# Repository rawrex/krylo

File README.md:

**Krylo** (*"wing"* in Russian) is a 32 key column-staggered split keyboard running [ZMK](https://zmk.dev/)

Core ideas that motivated the project:
- (My) pinky moves to the side better than it reaches forward to the upper row.
- (My) index finger is also able to move to the side, but it is not comfortable to move to the side and down.
- Single PCB symmetrical definition for both sides of the split.

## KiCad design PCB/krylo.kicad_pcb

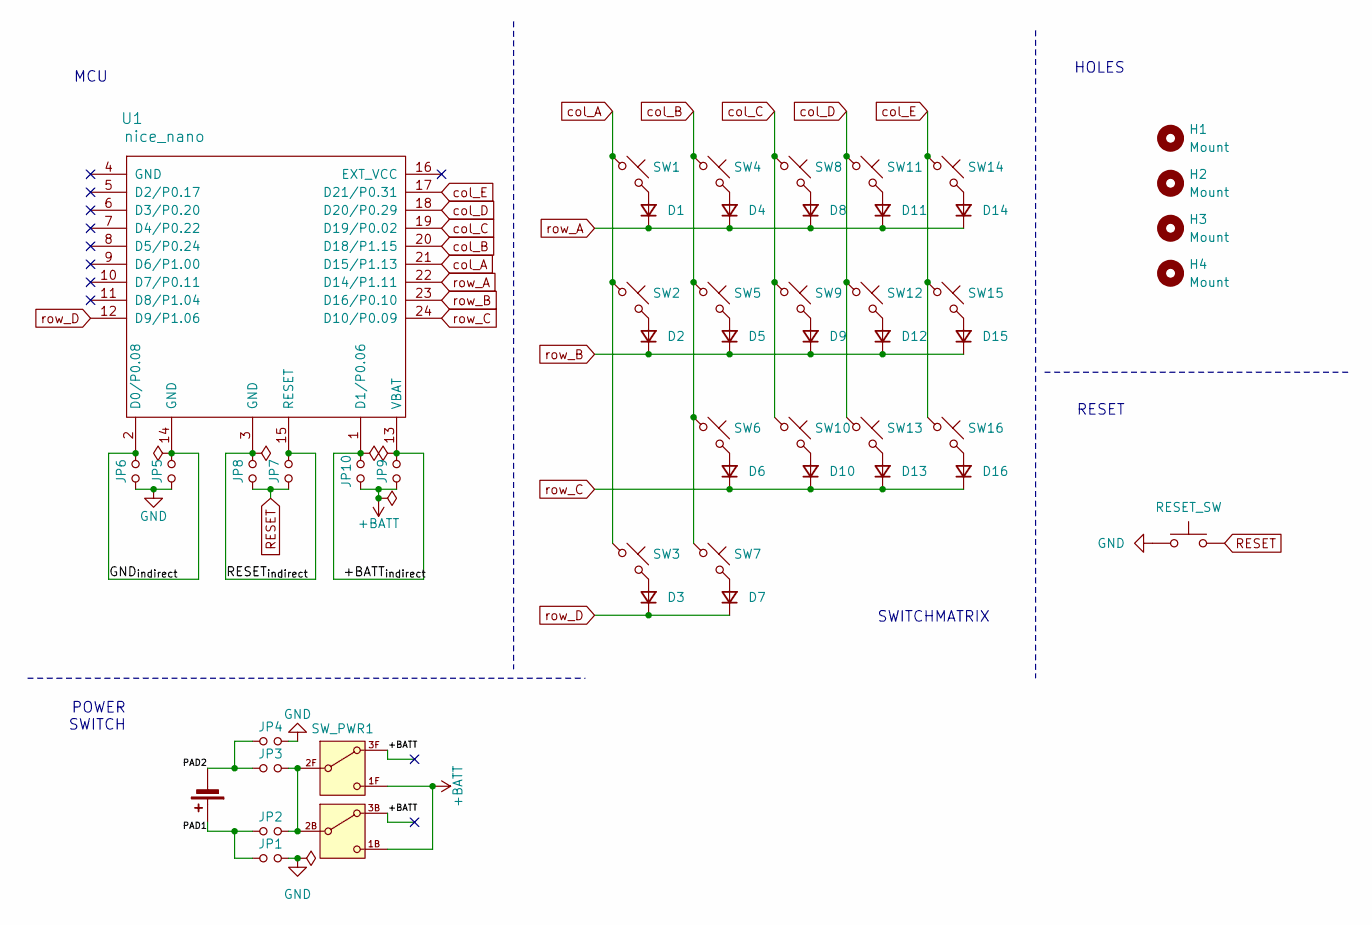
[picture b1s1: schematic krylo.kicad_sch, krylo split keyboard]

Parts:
BT1: MOLEX_C
D1, D2, D3, D4, D5, D6, D7, D8, D9, D10, D11, D12, D13, D14, D15, D16: D_SOD123
H1, H2, H3, H4: Mount
JP1, JP2, JP3, JP4, JP5, JP6, JP7, JP8, JP9, JP10: Jumper
RESET1: RESET_SW; ResetSW
SW1, SW2, SW3, SW4, SW5, SW6, SW7, SW8, SW9, SW10, SW11, SW12, SW13, SW14, SW15, SW16: Switch
SW_PWR1: MSK12C02
U1: nice_nano

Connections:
+BATT: JP9.1, JP10.1, SW_PWR1.1B (C_back), SW_PWR1.1F (C_front), SW_PWR1.3B (A_back), SW_PWR1.3F (A_front)
/+BATT_{indirect}: JP9.2, JP10.2, U1.1 (D1/P0.06), U1.13 (VBAT)
/GND_{indirect}: JP5.2, JP6.2, U1.2 (D0/P0.08), U1.14 (GND)
/PAD1: BT1.1 (+), JP1.1, JP2.1
/PAD2: BT1.2 (-), JP3.1, JP4.1
/RESET_{indirect}: JP7.2, JP8.2, U1.3 (GND), U1.15 (RESET)
GND: JP1.2, JP4.2, JP5.1, JP6.1, RESET1.1
unnamed: D1.2 (A), SW1.2
unnamed: D2.2 (A), SW2.2
unnamed: D3.2 (A), SW3.2
unnamed: D4.2 (A), SW4.2
unnamed: D5.2 (A), SW5.2
unnamed: D6.2 (A), SW6.2
unnamed: D7.2 (A), SW7.2
unnamed: D8.2 (A), SW8.2
unnamed: D9.2 (A), SW9.2
unnamed: D10.2 (A), SW10.2
unnamed: D11.2 (A), SW11.2
unnamed: D12.2 (A), SW12.2
unnamed: D13.2 (A), SW13.2
unnamed: D14.2 (A), SW14.2
unnamed: D15.2 (A), SW15.2
unnamed: D16.2 (A), SW16.2
unnamed: JP2.2, JP3.2, SW_PWR1.2B (B_back), SW_PWR1.2F (B_front)
RESET: JP7.1, JP8.1, RESET1.2
col_A: SW1.1, SW2.1, SW3.1, U1.21 (D15/P1.13)
col_B: SW4.1, SW5.1, SW6.1, SW7.1, U1.20 (D18/P1.15)
col_C: SW8.1, SW9.1, SW10.1, U1.19 (D19/P0.02)
col_D: SW11.1, SW12.1, SW13.1, U1.18 (D20/P0.29)
col_E: SW14.1, SW15.1, SW16.1, U1.17 (D21/P0.31)
row_A: D1.1 (K), D4.1 (K), D8.1 (K), D11.1 (K), D14.1 (K), U1.22 (D14/P1.11)
row_B: D2.1 (K), D5.1 (K), D9.1 (K), D12.1 (K), D15.1 (K), U1.23 (D16/P0.10)
row_C: D6.1 (K), D10.1 (K), D13.1 (K), D16.1 (K), U1.24 (D10/P0.09)
row_D: D3.1 (K), D7.1 (K), U1.12 (D9/P1.06)

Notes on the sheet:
SWITCHMATRIX
POWER SWITCH
HOLES
MCU
RESET

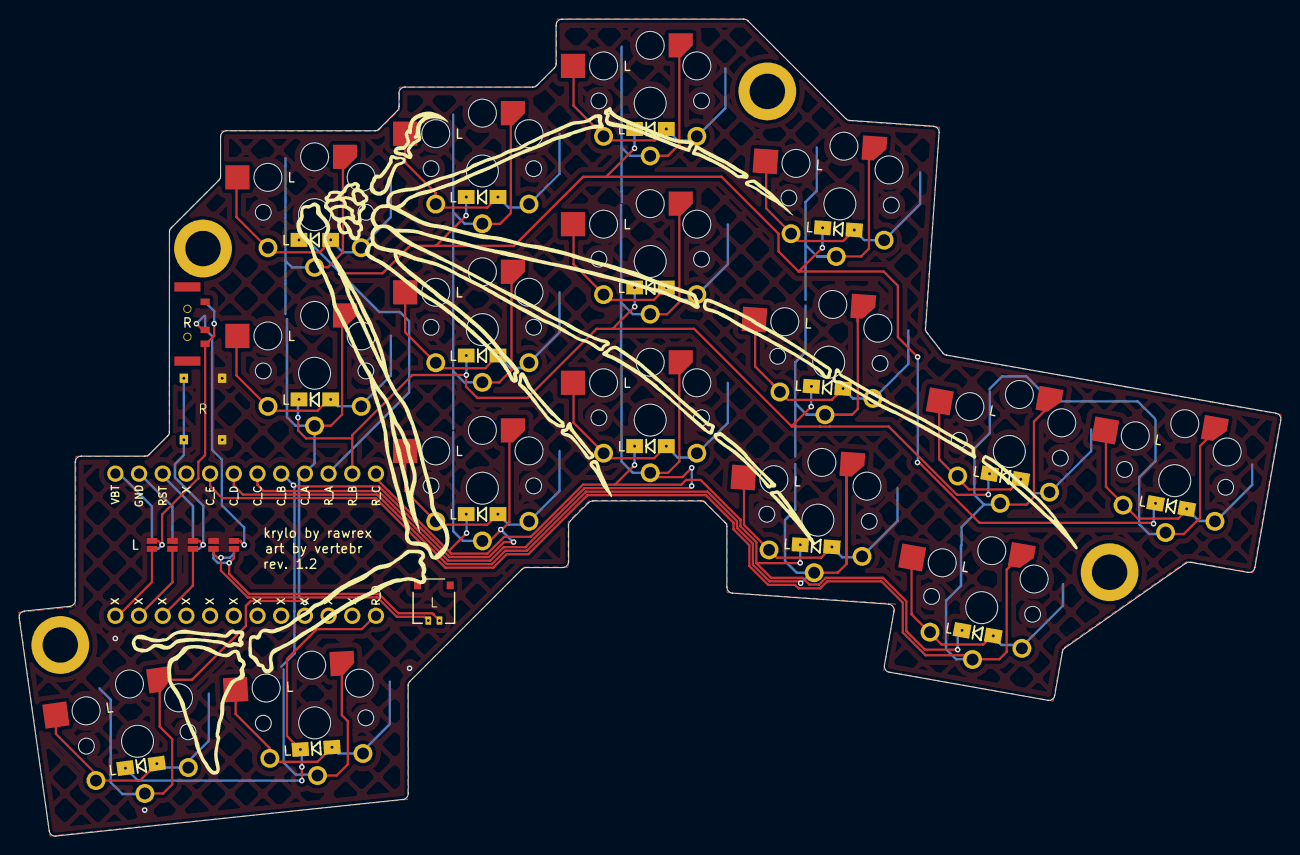
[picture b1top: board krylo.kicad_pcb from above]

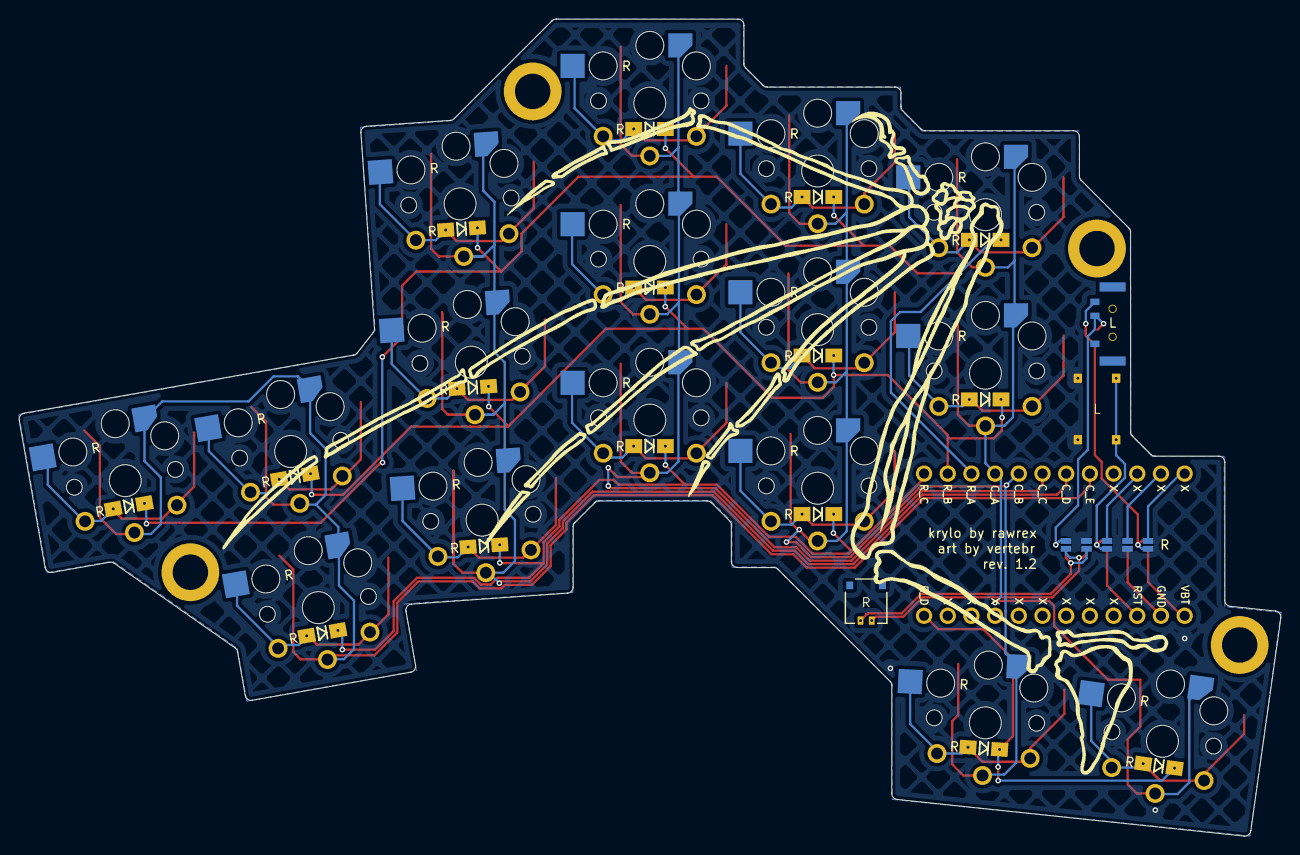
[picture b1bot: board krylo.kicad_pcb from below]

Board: 2 copper layers, 135.3 x 87.6 mm, 51 parts (5 on the bottom side), 34 nets.

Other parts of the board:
INFO: Info

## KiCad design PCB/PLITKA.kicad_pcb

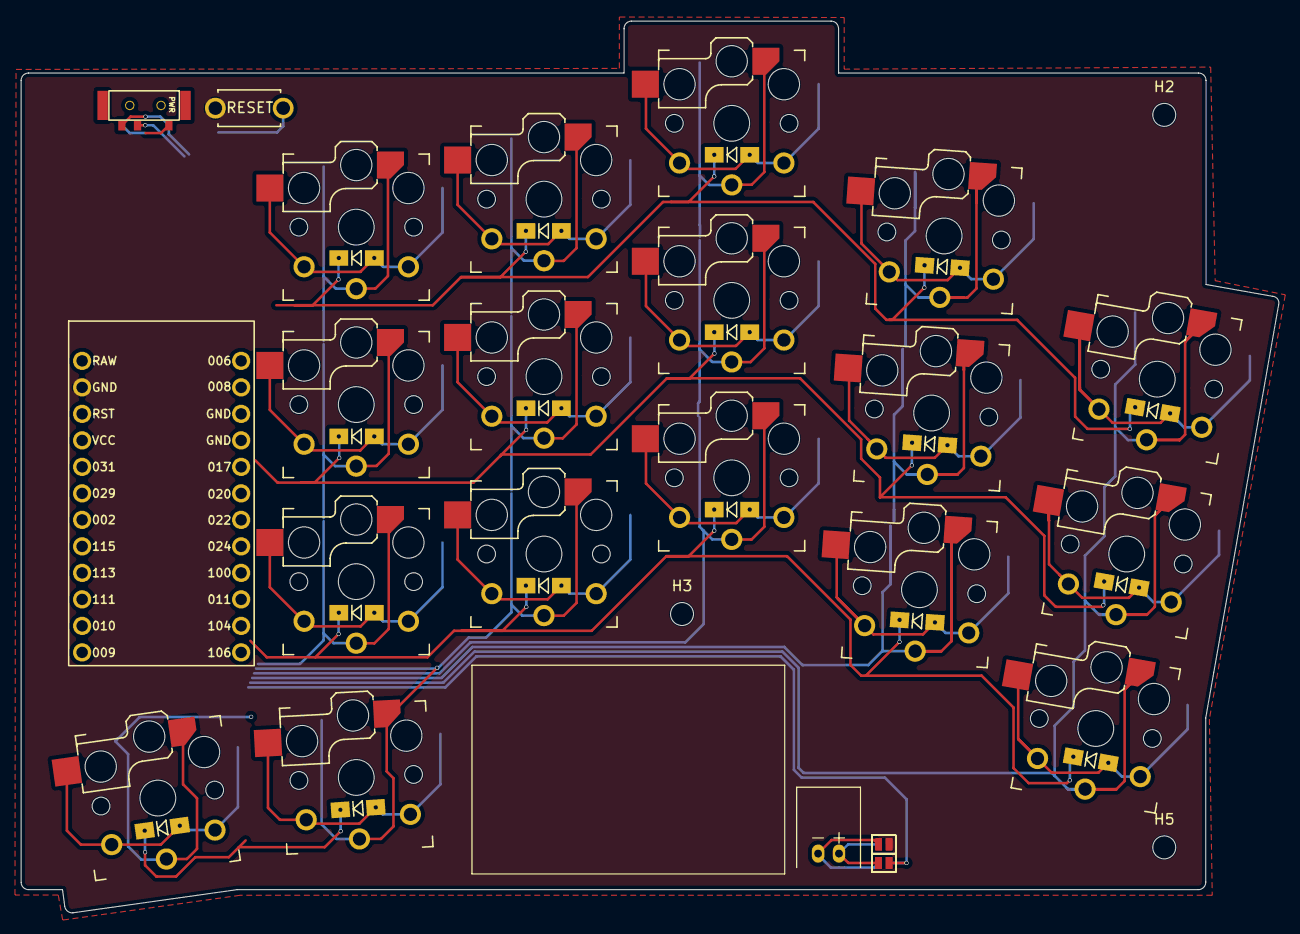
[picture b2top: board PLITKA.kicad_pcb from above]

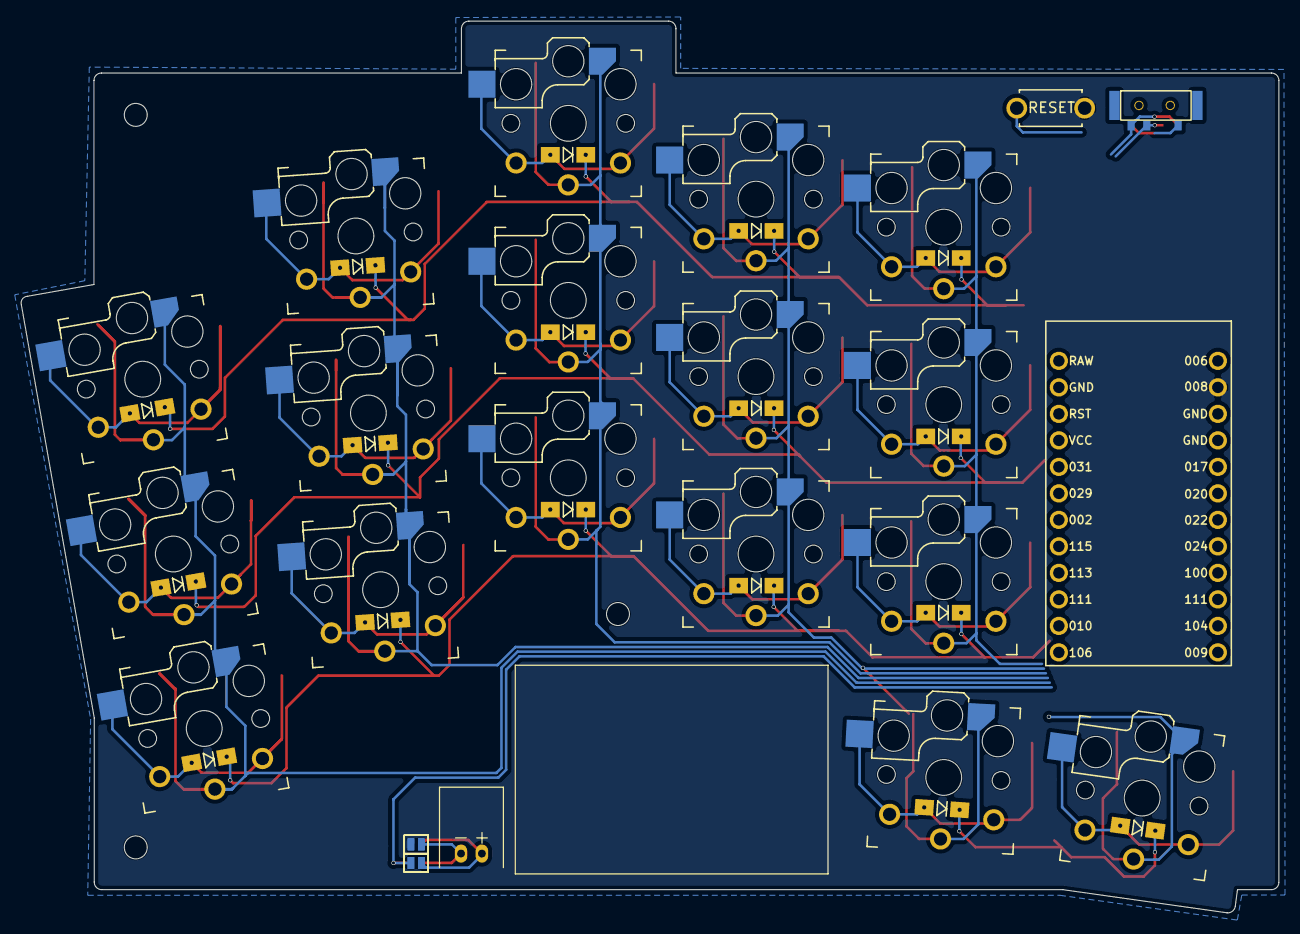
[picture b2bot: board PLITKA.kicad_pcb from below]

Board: 4 copper layers, 120.5 x 85.5 mm, 47 parts (2 on the bottom side), 32 nets.

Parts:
BT1: Battery_Cell; JST_PH_reversible
D1, D2, D3, D4, D5, D6, D7, D8, D9, D10, D11, D12, D13, D14, D15, D16, D17: D_Small; Diode_SOD123
H1, H2, H3, H4, H5: MountingHole; MountingHole_2.2mm_M2_ISO7380
JP1, JP2, JP3, JP4: Device_Jumper_NO_Small; Jumper
SW1: SW_SPDT_321; MSK12C02_reversible
SW2, SW3, SW4, SW5, SW6, SW7, SW8, SW9, SW10, SW11, SW12, SW13, SW14, SW15, SW16, SW17, SW18: MX_SW_HS; Kailh_socket_PG1350_optional_reversible
SW19: SW_Push; ResetSW
U1: nice!nano; nice_nano

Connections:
+BATT: SW1.3 (A), U1.16 (EXT_VCC)
/PAD1: BT1.1 (+), JP1.1, JP2.1
/PAD2: BT1.2 (-), JP3.1, JP4.1
GND: JP1.2, JP4.2, SW19.1, U1.14 (GND)
unnamed: D1.2 (A), SW2.2
unnamed: D2.2 (A), SW3.2
unnamed: D3.2 (A), SW4.2
unnamed: D4.2 (A), SW5.2
unnamed: D5.2 (A), SW6.2
unnamed: D6.2 (A), SW7.2
unnamed: D7.2 (A), SW8.2
unnamed: D8.2 (A), SW9.2
unnamed: D9.2 (A), SW10.2
unnamed: D10.2 (A), SW11.2
unnamed: D11.2 (A), SW12.2
unnamed: D12.2 (A), SW13.2
unnamed: D13.2 (A), SW14.2
unnamed: D14.2 (A), SW15.2
unnamed: D15.2 (A), SW16.2
unnamed: D16.2 (A), SW17.2
unnamed: D17.2 (A), SW18.2
unnamed: JP2.2, JP3.2, SW1.2 (B)
RESET: SW19.2, U1.15 (RESET)
col_A: SW2.1, SW3.1, SW4.1, SW5.1, U1.5 (D2/P0.17)
col_B: SW6.1, SW7.1, SW8.1, SW9.1, U1.6 (D3/P0.20)
col_C: SW10.1, SW11.1, SW12.1, U1.7 (D4/P0.22)
col_D: SW13.1, SW14.1, SW15.1, U1.8 (D5/P0.24)
col_E: SW16.1, SW17.1, SW18.1, U1.9 (D6/P1.00)
row_A: D1.1 (K), D5.1 (K), D9.1 (K), D12.1 (K), D15.1 (K), U1.10 (D7/P0.11)
row_B: D2.1 (K), D6.1 (K), D10.1 (K), D13.1 (K), D16.1 (K), U1.11 (D8/P1.04)
row_C: D3.1 (K), D7.1 (K), D11.1 (K), D14.1 (K), D17.1 (K), U1.12 (D9/P1.06)
row_D: D4.1 (K), D8.1 (K), U1.24 (D10/P0.09)

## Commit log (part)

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2026-06-12 No knub for the plitka
2026-06-12 No funding for the plitka
2026-06-12 Encoder connections are removed
2026-06-13 Non-JSC battery connection removed
2026-06-17 Pcb update
2026-06-17 Power flags errors correction
2026-06-17 Basic clean up of the Kalih sockets footprint
2026-06-18 Minor cosmetic correction
2026-06-18 Added missing pads on the B side
2026-06-18 Set up the board settings from the JLC PCB template
2026-06-18 Caps correction
2026-06-18 Added basic agents file
2026-06-18 Agents file update
2026-06-19 Case correction
2026-06-19 Rudimentary files clean up
2026-06-20 Updates pull
2026-06-20 Update from schematic
2026-06-20 Proper fill zones for the board
2026-06-22 PCB updates pull
2026-06-22 Power and reset switches with explicit references
2026-06-23 Configuration jumpers for GPIO pins on the MCU
2026-06-23 Designators clean up
2026-06-26 Existing 3D models clean up and addition of the hot swap for the switch footprint
2026-06-26 Added a 3D model
2026-06-26 Readme update. Started to outline the concept of the board
2026-06-28 Routes configuration in process
2026-06-29 Routing clean up
2026-06-29 Board edge clearance violations fix
2026-06-29 Missing backside courtyard added
2026-06-29 Shapes autoheal
2026-06-29 Corrected 3D model offset
2026-06-29 Internalized the mounting hole footprint to clean it up and to remove the DRC warning
2026-06-30 Corrected the layers property of the connections on the reset component
2026-06-30 Pulled updates
2026-06-30 Fixed the silkscreen clipping warning
2026-06-30 More tracks clean up
2026-06-30 Explicit track to GND from the RESET pin
2026-06-30 Adedd few explicit DRC exclusions
2026-06-30 Defaults update
2026-06-30 Typo fix
2026-06-30 Filenames clean up for consistency
2026-06-30 Rudimentary lines cleaned out of the symbol
2026-06-30 Footprints clean up
2026-06-30 Consistent field values
